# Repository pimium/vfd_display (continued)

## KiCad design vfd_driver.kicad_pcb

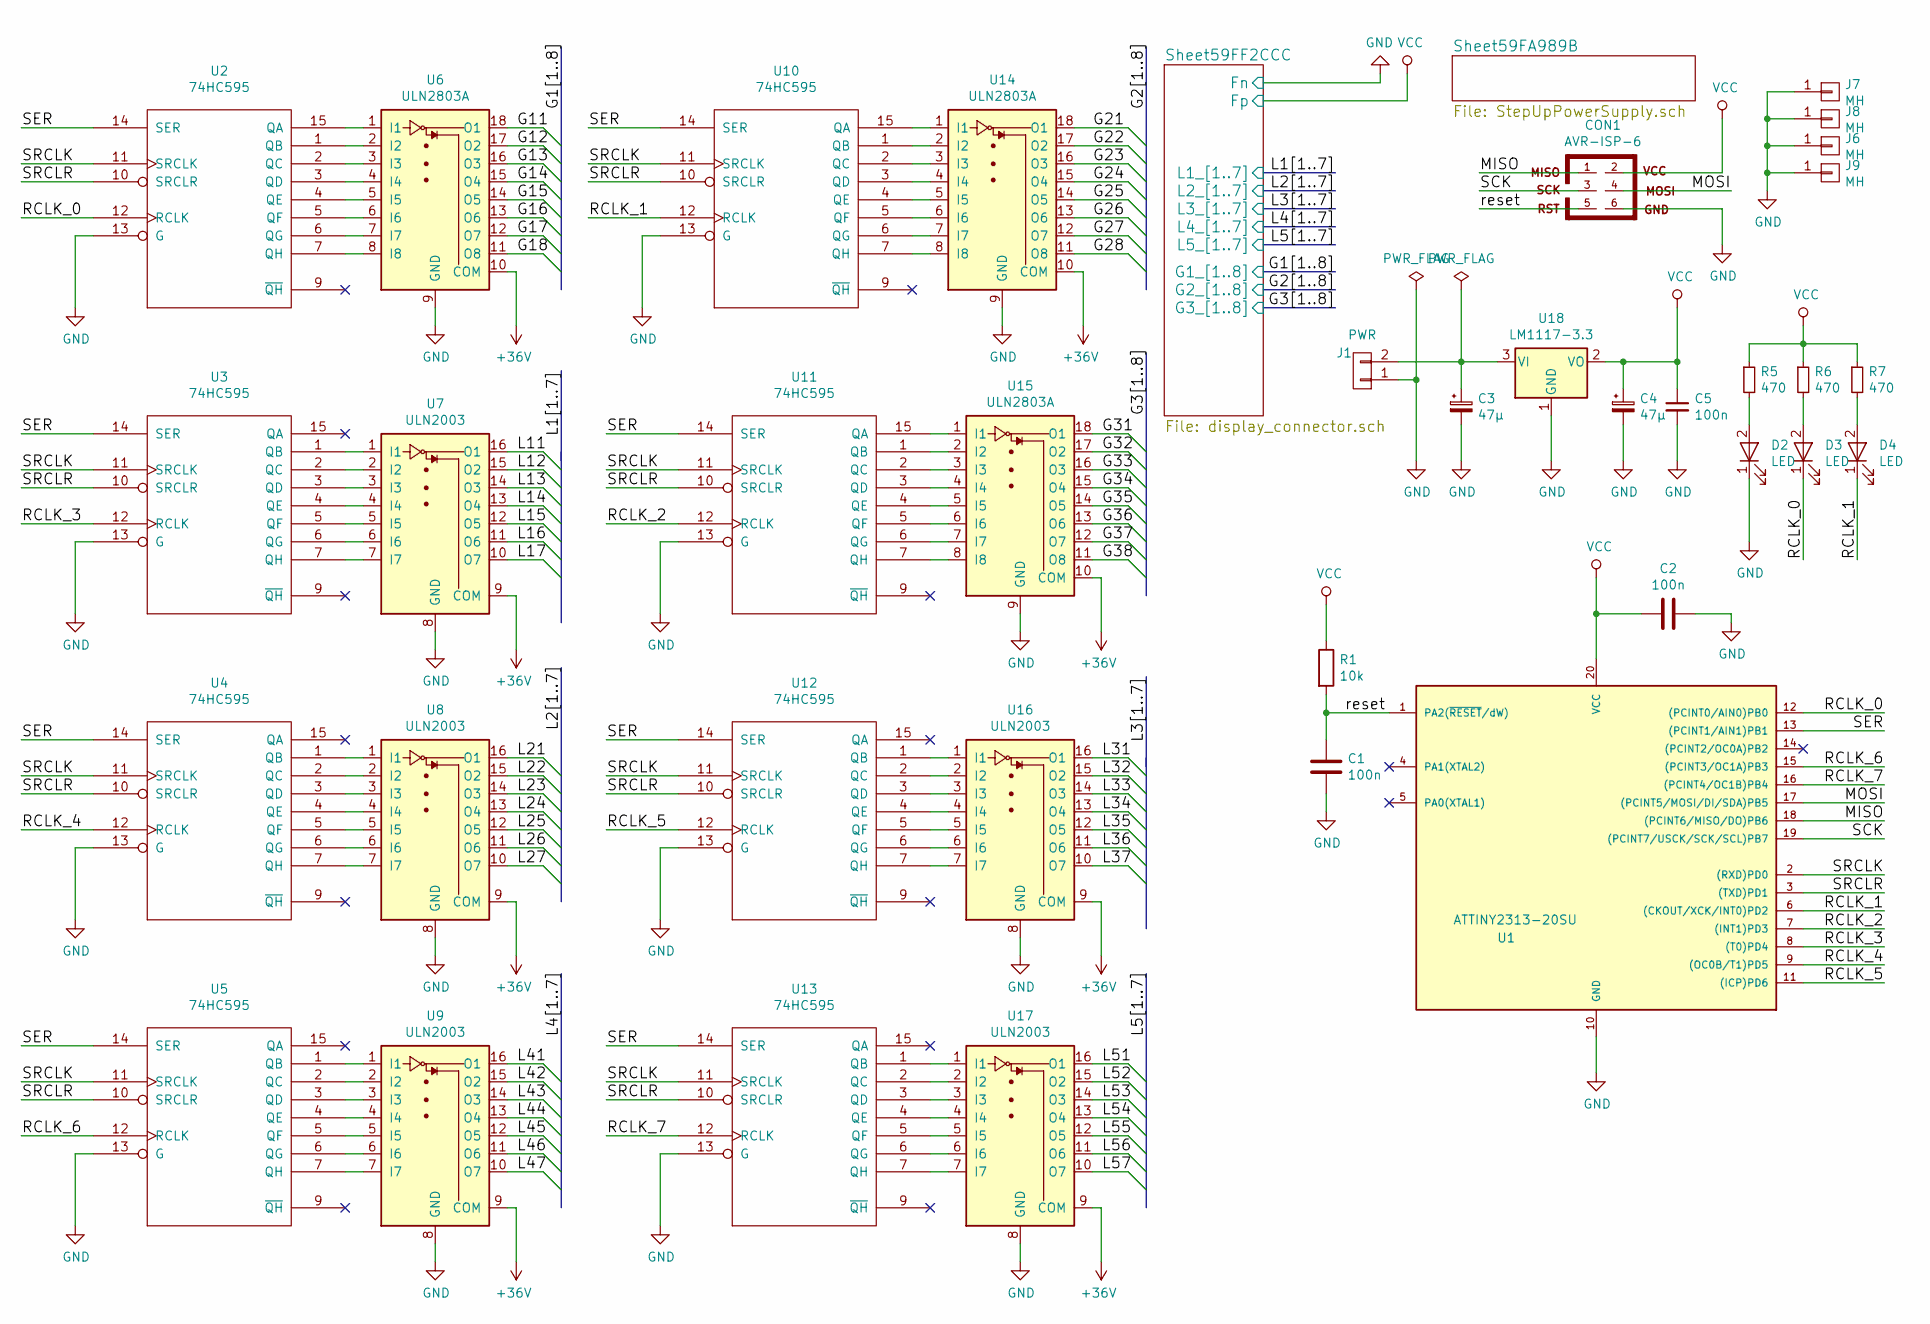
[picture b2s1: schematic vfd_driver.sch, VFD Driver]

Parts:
C1, C2, C5: 100n; C_0805_HandSoldering
C3, C4: 47µ; CP_Radial_Tantal_D4.5mm_P2.50mm
CON1: AVR-ISP-6; Pin_Header_Straight_2x03_Pitch2.54mm_SMD
D2, D3, D4: LED; LED_0805
J1: PWR; PINHEAD1-2
J6, J7, J8, J9: MH; MountingHole_3.2mm_M3_DIN965_Pad
R1: 10k; R_1206
R5, R6, R7: 470; R_1206
U1: ATTINY2313-20SU; SOIC-20W_7.5x12.8mm_Pitch1.27mm
U2, U3, U4, U5, U10, U11, U12, U13: 74HC595; SOIC-16_3.9x9.9mm_Pitch1.27mm
U6, U14, U15: ULN2803A; SOIC-18W_7.5x11.6mm_Pitch1.27mm
U7, U8, U9, U16, U17: ULN2003; SOIC-16_3.9x9.9mm_Pitch1.27mm
U18: LM1117-3.3; SOT-223_pin4_3

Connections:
+36V: U6.10 (COM), U7.9 (COM), U8.9 (COM), U9.9 (COM), U14.10 (COM), U15.10 (COM), U16.9 (COM), U17.9 (COM); also elsewhere on the board
/G11: U6.18 (O1); also elsewhere on the board
/G12: U6.17 (O2); also elsewhere on the board
/G13: U6.16 (O3); also elsewhere on the board
/G14: U6.15 (O4); also elsewhere on the board
/G15: U6.14 (O5); also elsewhere on the board
/G16: U6.13 (O6); also elsewhere on the board
/G17: U6.12 (O7); also elsewhere on the board
/G18: U6.11 (O8); also elsewhere on the board
/G21: U14.18 (O1); also elsewhere on the board
/G22: U14.17 (O2); also elsewhere on the board
/G23: U14.16 (O3); also elsewhere on the board
/G24: U14.15 (O4); also elsewhere on the board
/G25: U14.14 (O5); also elsewhere on the board
/G26: U14.13 (O6); also elsewhere on the board
/G27: U14.12 (O7); also elsewhere on the board
/G28: U14.11 (O8); also elsewhere on the board
/G31: U15.18 (O1); also elsewhere on the board
/G32: U15.17 (O2); also elsewhere on the board
/G33: U15.16 (O3); also elsewhere on the board
/G34: U15.15 (O4); also elsewhere on the board
/G35: U15.14 (O5); also elsewhere on the board
/G36: U15.13 (O6); also elsewhere on the board
/G37: U15.12 (O7); also elsewhere on the board
/G38: U15.11 (O8); also elsewhere on the board
/L11: U7.16 (O1); also elsewhere on the board
/L12: U7.15 (O2); also elsewhere on the board
/L13: U7.14 (O3); also elsewhere on the board
/L14: U7.13 (O4); also elsewhere on the board
/L15: U7.12 (O5); also elsewhere on the board
/L16: U7.11 (O6); also elsewhere on the board
/L17: U7.10 (O7); also elsewhere on the board
/L21: U8.16 (O1); also elsewhere on the board
/L22: U8.15 (O2); also elsewhere on the board
/L23: U8.14 (O3); also elsewhere on the board
/L24: U8.13 (O4); also elsewhere on the board
/L25: U8.12 (O5); also elsewhere on the board
/L26: U8.11 (O6); also elsewhere on the board
/L27: U8.10 (O7); also elsewhere on the board
/L31: U16.16 (O1); also elsewhere on the board
/L32: U16.15 (O2); also elsewhere on the board
/L33: U16.14 (O3); also elsewhere on the board
/L34: U16.13 (O4); also elsewhere on the board
/L35: U16.12 (O5); also elsewhere on the board
/L36: U16.11 (O6); also elsewhere on the board
/L37: U16.10 (O7); also elsewhere on the board
/L41: U9.16 (O1); also elsewhere on the board
/L42: U9.15 (O2); also elsewhere on the board
/L43: U9.14 (O3); also elsewhere on the board
/L44: U9.13 (O4); also elsewhere on the board
/L45: U9.12 (O5); also elsewhere on the board
/L46: U9.11 (O6); also elsewhere on the board
/L47: U9.10 (O7); also elsewhere on the board
/L51: U17.16 (O1); also elsewhere on the board
/L52: U17.15 (O2); also elsewhere on the board
/L53: U17.14 (O3); also elsewhere on the board
/L54: U17.13 (O4); also elsewhere on the board
/L55: U17.12 (O5); also elsewhere on the board
/L56: U17.11 (O6); also elsewhere on the board
/L57: U17.10 (O7); also elsewhere on the board
/MISO: CON1.1, U1.18 ((PCINT6/MISO/DO)PB6)
/MOSI: CON1.4, U1.17 ((PCINT5/MOSI/DI/SDA)PB5)
/RCLK_0: D3.1 (K), U1.12 ((PCINT0/AIN0)PB0), U2.12 (RCLK)
/RCLK_1: D4.1 (K), U1.6 ((CKOUT/XCK/INT0)PD2), U10.12 (RCLK)
/RCLK_2: U1.7 ((INT1)PD3), U11.12 (RCLK)
/RCLK_3: U1.8 ((T0)PD4), U3.12 (RCLK)
/RCLK_4: U1.9 ((OC0B/T1)PD5), U4.12 (RCLK)
/RCLK_5: U1.11 ((ICP)PD6), U12.12 (RCLK)
/RCLK_6: U1.15 ((PCINT3/OC1A)PB3), U5.12 (RCLK)
/RCLK_7: U1.16 ((PCINT4/OC1B)PB4), U13.12 (RCLK)
/SCK: CON1.3, U1.19 ((PCINT7/USCK/SCK/SCL)PB7)
/SER: U1.13 ((PCINT1/AIN1)PB1), U2.14 (SER), U3.14 (SER), U4.14 (SER), U5.14 (SER), U10.14 (SER), U11.14 (SER), U12.14 (SER), U13.14 (SER)
/SRCLK: U1.2 ((RXD)PD0), U2.11 (SRCLK), U3.11 (SRCLK), U4.11 (SRCLK), U5.11 (SRCLK), U10.11 (SRCLK), U11.11 (SRCLK), U12.11 (SRCLK), U13.11 (SRCLK)
/SRCLR: U1.3 ((TXD)PD1), U2.10 (SRCLR), U3.10 (SRCLR), U4.10 (SRCLR), U5.10 (SRCLR), U10.10 (SRCLR), U11.10 (SRCLR), U12.10 (SRCLR), U13.10 (SRCLR)
/reset: C1.1, CON1.5, R1.2, U1.1 (PA2(~RESET~/dW))
GND: C1.2, C2.1, C3.2, C4.2, C5.2, CON1.6, D2.1 (K), J1.1, J6.1, J7.1, J8.1, J9.1, U1.10 (GND), U2.8 (GND), U2.13 (G), U3.8 (GND), U3.13 (G), U4.8 (GND), U4.13 (G), U5.8 (GND), U5.13 (G), U6.9 (GND), U7.8 (GND), U8.8 (GND), U9.8 (GND), U10.8 (GND), U10.13 (G), U11.8 (GND), U11.13 (G), U12.8 (GND), U12.13 (G), U13.8 (GND), U13.13 (G), U14.9 (GND), U15.9 (GND), U16.8 (GND), U17.8 (GND), U18.1 (GND); also elsewhere on the board
unnamed: C3.1, J1.2, U18.3 (VI)
unnamed: D2.2 (A), R5.2
unnamed: D3.2 (A), R6.2
unnamed: D4.2 (A), R7.2
unnamed: U2.1 (QB), U6.2 (I2)
unnamed: U2.2 (QC), U6.3 (I3)
unnamed: U2.3 (QD), U6.4 (I4)
unnamed: U2.4 (QE), U6.5 (I5)
unnamed: U2.5 (QF), U6.6 (I6)
unnamed: U2.6 (QG), U6.7 (I7)
unnamed: U2.7 (QH), U6.8 (I8)
unnamed: U2.15 (QA), U6.1 (I1)
unnamed: U3.1 (QB), U7.1 (I1)
unnamed: U3.2 (QC), U7.2 (I2)
unnamed: U3.3 (QD), U7.3 (I3)
unnamed: U3.4 (QE), U7.4 (I4)
unnamed: U3.5 (QF), U7.5 (I5)
unnamed: U3.6 (QG), U7.6 (I6)
unnamed: U3.7 (QH), U7.7 (I7)
unnamed: U4.1 (QB), U8.1 (I1)
unnamed: U4.2 (QC), U8.2 (I2)
unnamed: U4.3 (QD), U8.3 (I3)
unnamed: U4.4 (QE), U8.4 (I4)
unnamed: U4.5 (QF), U8.5 (I5)
unnamed: U4.6 (QG), U8.6 (I6)
unnamed: U4.7 (QH), U8.7 (I7)
unnamed: U5.1 (QB), U9.1 (I1)
unnamed: U5.2 (QC), U9.2 (I2)
unnamed: U5.3 (QD), U9.3 (I3)
unnamed: U5.4 (QE), U9.4 (I4)
unnamed: U5.5 (QF), U9.5 (I5)
unnamed: U5.6 (QG), U9.6 (I6)
unnamed: U5.7 (QH), U9.7 (I7)
unnamed: U10.1 (QB), U14.2 (I2)
unnamed: U10.2 (QC), U14.3 (I3)
unnamed: U10.3 (QD), U14.4 (I4)
unnamed: U10.4 (QE), U14.5 (I5)
unnamed: U10.5 (QF), U14.6 (I6)
unnamed: U10.6 (QG), U14.7 (I7)
unnamed: U10.7 (QH), U14.8 (I8)
unnamed: U10.15 (QA), U14.1 (I1)
unnamed: U11.1 (QB), U15.2 (I2)
unnamed: U11.2 (QC), U15.3 (I3)
unnamed: U11.3 (QD), U15.4 (I4)
unnamed: U11.4 (QE), U15.5 (I5)
unnamed: U11.5 (QF), U15.6 (I6)
unnamed: U11.6 (QG), U15.7 (I7)
unnamed: U11.7 (QH), U15.8 (I8)
unnamed: U11.15 (QA), U15.1 (I1)
unnamed: U12.1 (QB), U16.1 (I1)
unnamed: U12.2 (QC), U16.2 (I2)
unnamed: U12.3 (QD), U16.3 (I3)
unnamed: U12.4 (QE), U16.4 (I4)
unnamed: U12.5 (QF), U16.5 (I5)
unnamed: U12.6 (QG), U16.6 (I6)
unnamed: U12.7 (QH), U16.7 (I7)
unnamed: U13.1 (QB), U17.1 (I1)
unnamed: U13.2 (QC), U17.2 (I2)
unnamed: U13.3 (QD), U17.3 (I3)
unnamed: U13.4 (QE), U17.4 (I4)
unnamed: U13.5 (QF), U17.5 (I5)
unnamed: U13.6 (QG), U17.6 (I6)
unnamed: U13.7 (QH), U17.7 (I7)
VCC: C2.2, C4.1, C5.1, CON1.2, R1.1, R5.1, R6.1, R7.1, U1.20 (VCC), U2.16 (VCC), U3.16 (VCC), U4.16 (VCC), U5.16 (VCC), U10.16 (VCC), U11.16 (VCC), U12.16 (VCC), U13.16 (VCC), U18.2 (VO); also elsewhere on the board

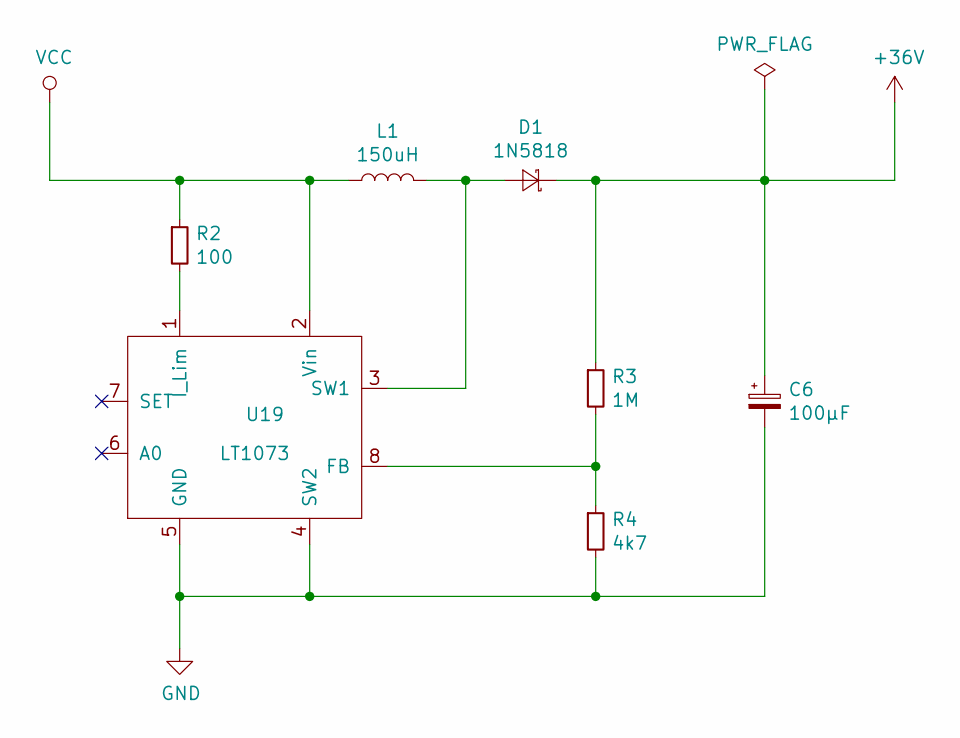
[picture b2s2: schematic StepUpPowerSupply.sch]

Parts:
C6: 100µF; CP_Elec_8x5.4
D1: 1N5818; D_SMA_Handsoldering
L1: 150uH; Choke_CD75
R2: 100; R_1206
R3: 1M; R_1206
R4: 4k7; R_1206
U19: LT1073; SOIC-8_3.9x4.9mm_Pitch1.27mm

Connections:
+36V: C6.1, D1.1 (K), R3.1; also elsewhere on the board
GND: C6.2, R4.2, U19.4 (SW2), U19.5 (GND); also elsewhere on the board
unnamed: D1.2 (A), L1.2, U19.3 (SW1)
unnamed: R2.2, U19.1 (I_Lim)
unnamed: R3.2, R4.1, U19.8 (FB)
VCC: L1.1, R2.1, U19.2 (Vin); also elsewhere on the board

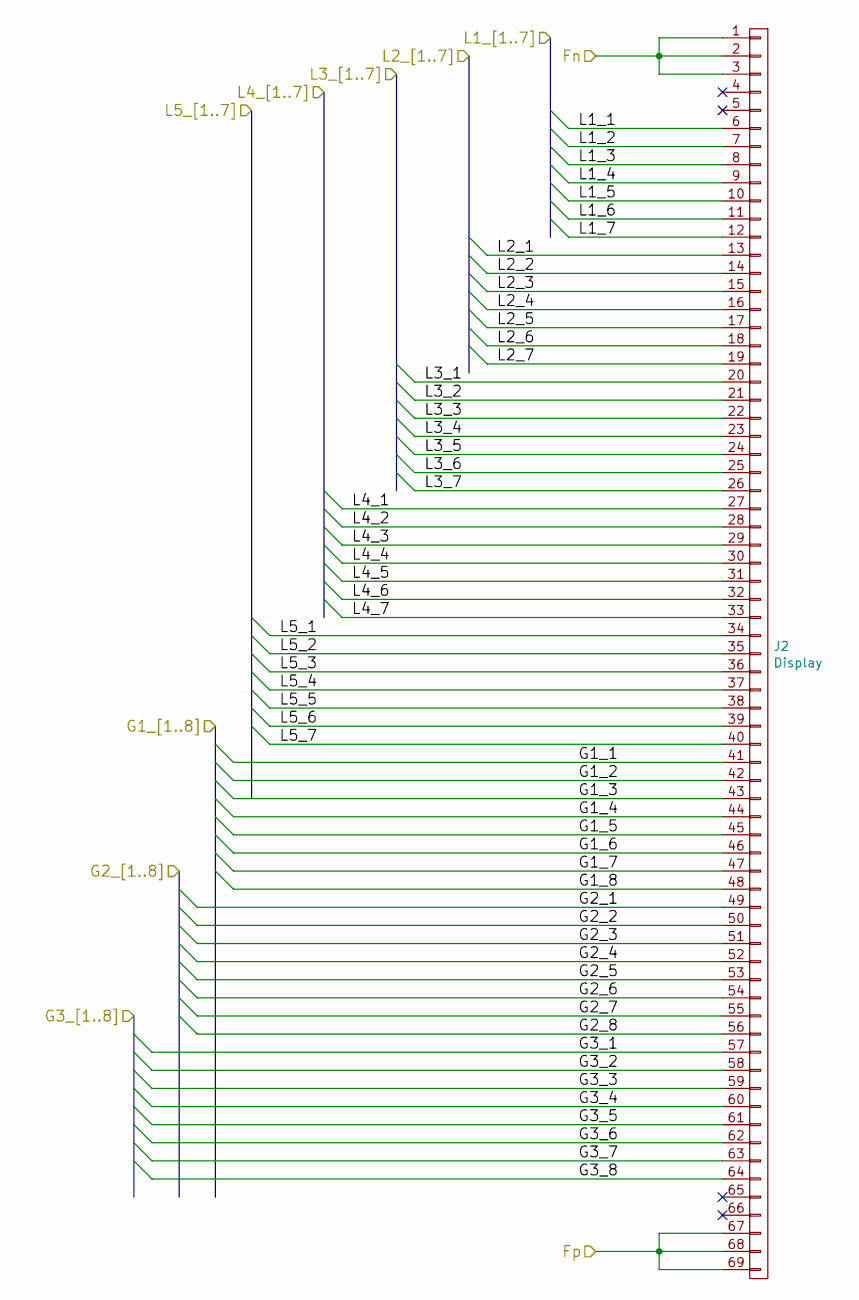
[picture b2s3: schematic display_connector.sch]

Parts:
J2: Display; vfd_FUTABA_24-SD-01GK_24x1

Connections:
/G11: J2.41; also elsewhere on the board
/G12: J2.42; also elsewhere on the board
/G13: J2.43; also elsewhere on the board
/G14: J2.44; also elsewhere on the board
/G15: J2.45; also elsewhere on the board
/G16: J2.46; also elsewhere on the board
/G17: J2.47; also elsewhere on the board
/G18: J2.48; also elsewhere on the board
/G21: J2.49; also elsewhere on the board
/G22: J2.50; also elsewhere on the board
/G23: J2.51; also elsewhere on the board
/G24: J2.52; also elsewhere on the board
/G25: J2.53; also elsewhere on the board
/G26: J2.54; also elsewhere on the board
/G27: J2.55; also elsewhere on the board
/G28: J2.56; also elsewhere on the board
/G31: J2.57; also elsewhere on the board
/G32: J2.58; also elsewhere on the board
/G33: J2.59; also elsewhere on the board
/G34: J2.60; also elsewhere on the board
/G35: J2.61; also elsewhere on the board
/G36: J2.62; also elsewhere on the board
/G37: J2.63; also elsewhere on the board
/G38: J2.64; also elsewhere on the board
/L11: J2.6; also elsewhere on the board
/L12: J2.7; also elsewhere on the board
/L13: J2.8; also elsewhere on the board
/L14: J2.9; also elsewhere on the board
/L15: J2.10; also elsewhere on the board
/L16: J2.11; also elsewhere on the board
/L17: J2.12; also elsewhere on the board
/L21: J2.13; also elsewhere on the board
/L22: J2.14; also elsewhere on the board
/L23: J2.15; also elsewhere on the board
/L24: J2.16; also elsewhere on the board
/L25: J2.17; also elsewhere on the board
/L26: J2.18; also elsewhere on the board
/L27: J2.19; also elsewhere on the board
/L31: J2.20; also elsewhere on the board
/L32: J2.21; also elsewhere on the board
/L33: J2.22; also elsewhere on the board
/L34: J2.23; also elsewhere on the board
/L35: J2.24; also elsewhere on the board
/L36: J2.25; also elsewhere on the board
/L37: J2.26; also elsewhere on the board
/L41: J2.27; also elsewhere on the board
/L42: J2.28; also elsewhere on the board
/L43: J2.29; also elsewhere on the board
/L44: J2.30; also elsewhere on the board
/L45: J2.31; also elsewhere on the board
/L46: J2.32; also elsewhere on the board
/L47: J2.33; also elsewhere on the board
/L51: J2.34; also elsewhere on the board
/L52: J2.35; also elsewhere on the board
/L53: J2.36; also elsewhere on the board
/L54: J2.37; also elsewhere on the board
/L55: J2.38; also elsewhere on the board
/L56: J2.39; also elsewhere on the board
/L57: J2.40; also elsewhere on the board
GND: J2.1, J2.2, J2.3; also elsewhere on the board
VCC: J2.67, J2.68, J2.69; also elsewhere on the board

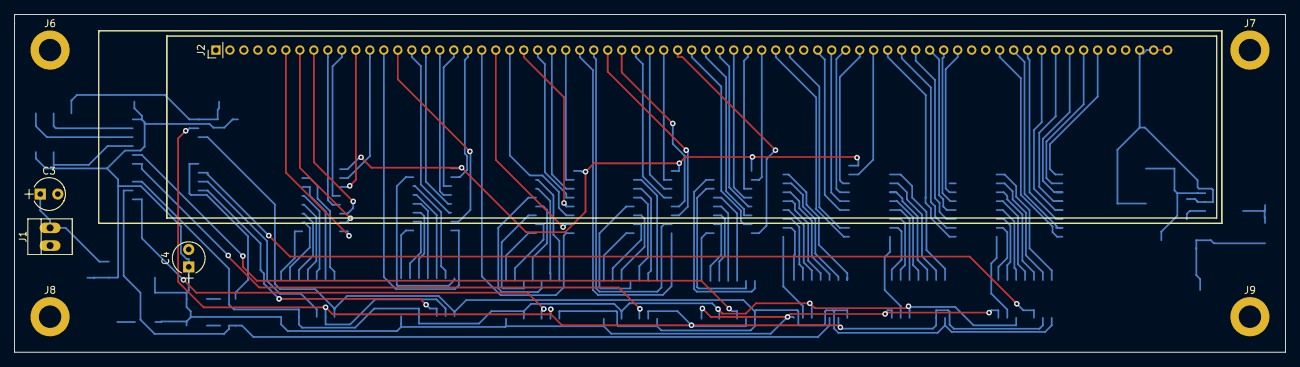
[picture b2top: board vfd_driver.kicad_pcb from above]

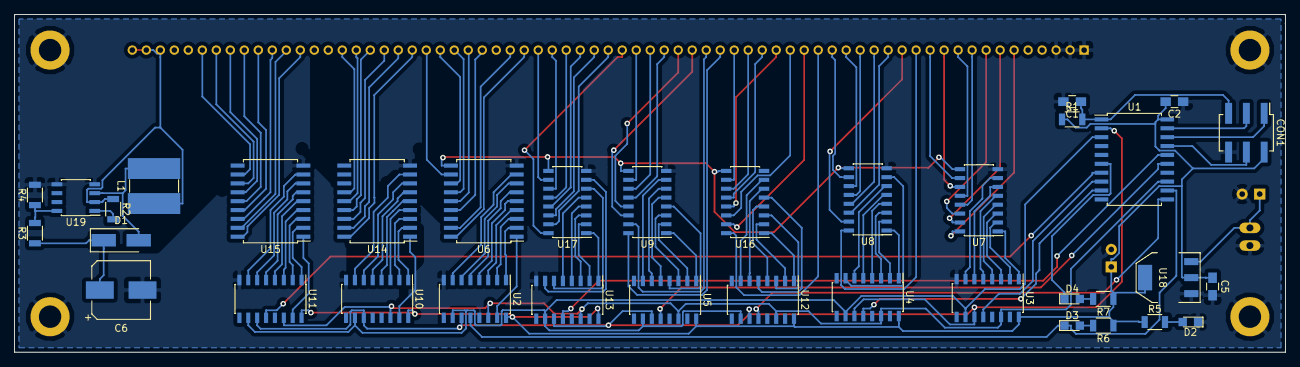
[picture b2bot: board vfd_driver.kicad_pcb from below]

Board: 2 copper layers, 181.6 x 48.3 mm, 44 parts (36 on the bottom side), 143 nets.

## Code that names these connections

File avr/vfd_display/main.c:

/*************************************************************************
Title:    Example program for the Interrupt controlled UART library
Author:   Peter Fleury <pfleury@gmx.ch>   http://tinyurl.com/peterfleury
File:     $Id: test_uart.c,v 1.7 2015/01/31 17:46:31 peter Exp $
Software: AVR-GCC 4.x
Hardware: AVR with built-in UART/USART

DESCRIPTION:
          This example shows how to use the UART library uart.c

*************************************************************************/
#include <avr/interrupt.h>
#include <avr/io.h>
#include <avr/pgmspace.h>
#include <stdlib.h>

/* define CPU frequency in Hz in Makefile */
#ifndef F_CPU
#error "F_CPU undefined, please define CPU frequency in Hz in Makefile"
#endif

/* Define UART buad rate here */
#define UART_BAUD_RATE 9600

void *state_idle(void);
void *state_clk_low(void);
void *state_clk_high(void);
void SR_write(uint8_t reg, uint8_t data);

volatile uint8_t busy_flag = 1;
volatile uint8_t data_flag = 0;
volatile uint8_t data_register = 0;
volatile uint8_t shift_register = 0;
volatile uint8_t count_flag = 0;

// State pointer
typedef void *(*StateFunc)(void);
StateFunc statefunc = state_idle;

void SR_write(uint8_t reg, uint8_t data){
  busy_flag = 1;
  shift_register = reg;
  data_register = data;
  count_flag = 8;
  data_flag = 1;
  while(busy_flag);
  return;
}

// States
void *state_idle(void)
{
  
  PORTD &= ~(1 << PD0);
  
  if (data_flag)
  {
    data_flag = 0;
    return state_clk_low;
  }
  busy_flag = 0;
  return state_idle;
}

void *state_rclk_low(void)
{
  busy_flag = 1;
  switch(shift_register) {
    case 0:
      PORTB &= ~(1 << PB0);
      break;
      case 1:
        PORTD &= ~(1 << PD2);
        break;
      case 2:
        PORTD &= ~(1 << PD3);
        break;
      case 3:
        PORTD &= ~(1 << PD4);
        break;
      case 4:
        PORTD &= ~(1 << PD5);
        break;
      case 5:
        PORTD &= ~(1 << PD6);
        break;
      case 6:
         PORTB &= ~(1 << PB3);
         break;
      case 7:
         PORTB &= ~(1 << PB4);
         break;
      default:
        break;
      }
  return state_idle;
}

void *state_rclk_high(void)
{
  busy_flag = 1;
  PORTB |= ((1 << PB0) | (1 << PB3) | (1 << PB4));
  PORTD |= ((1 << PD2) | (1 << PD3) | (1 << PD4) | (1 << PD5) | (1 << PD6));
  return state_rclk_low;
}

void *state_clk_low(void)
{
  PORTD &= ~(1 << PD0);
  busy_flag = 1;
  if (!count_flag)
  {
    return state_rclk_high;
  }
  count_flag--;
  if (data_register & (1 << 7))
  {
    PORTB |= (1 << PB1);
  }else
    PORTB &= ~(1 << PB1);
  data_register = data_register << 1;
  return state_clk_high;
}



void *state_clk_high(void)
{
  busy_flag = 1;
  PORTD |= (1 << PD0);
  return state_clk_low;
}

ISR(TIMER0_OVF_vect)
{
  PORTA ^= (1 << PA1);
  PORTA ^= (1 << PA0);
  statefunc = (StateFunc)(*statefunc)();
  return;
}

int main(void)
{

  DDRD |= ((1 << PD0) | (1 << PD1) | (1 << PD2) | (1 << PD3) | (1 << PD4) | (1 << PD5) | (1 << PD6));
  DDRB |= ((1 << PB0) | (1 << PB1) | (1 << PB3) | (1 << PB4));
  DDRA |= ((1 << PA0) | (1 << PA1));

  PORTD &= ~(1 << PD1);
  // Timer 0 konfigurieren
  TCCR0B = (0 << CS02) | (1 << CS00); // Prescaler
  // TCCR0B = 0; // Disable timer

  // TIMSK |= (1 << OCIE0A); // Interrupt on compare A match erlauben
  TIMSK |= (1 << TOIE0); // Timer Overflow Interrupt

  // Global Interrupts aktivieren
  sei();

  SR_write(0, 0x20);
    while(busy_flag);

  /* loop */
  while (1)
  {
    PORTD |= (1 << PD1);
    
    for (int i = 0; i < 8; ++i)
    {
      SR_write(0, (1 << i));
    }
    // statefunc = state_clk_high;
  }
  return 1;
}

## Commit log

2017-11-13 first version
2017-11-13 add avr files
2017-11-23 routing
2017-12-03 Not working need high side driver
